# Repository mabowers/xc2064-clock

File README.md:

# xc2064-clock
Desk clock based on the Xilinx XC2064 FPGA

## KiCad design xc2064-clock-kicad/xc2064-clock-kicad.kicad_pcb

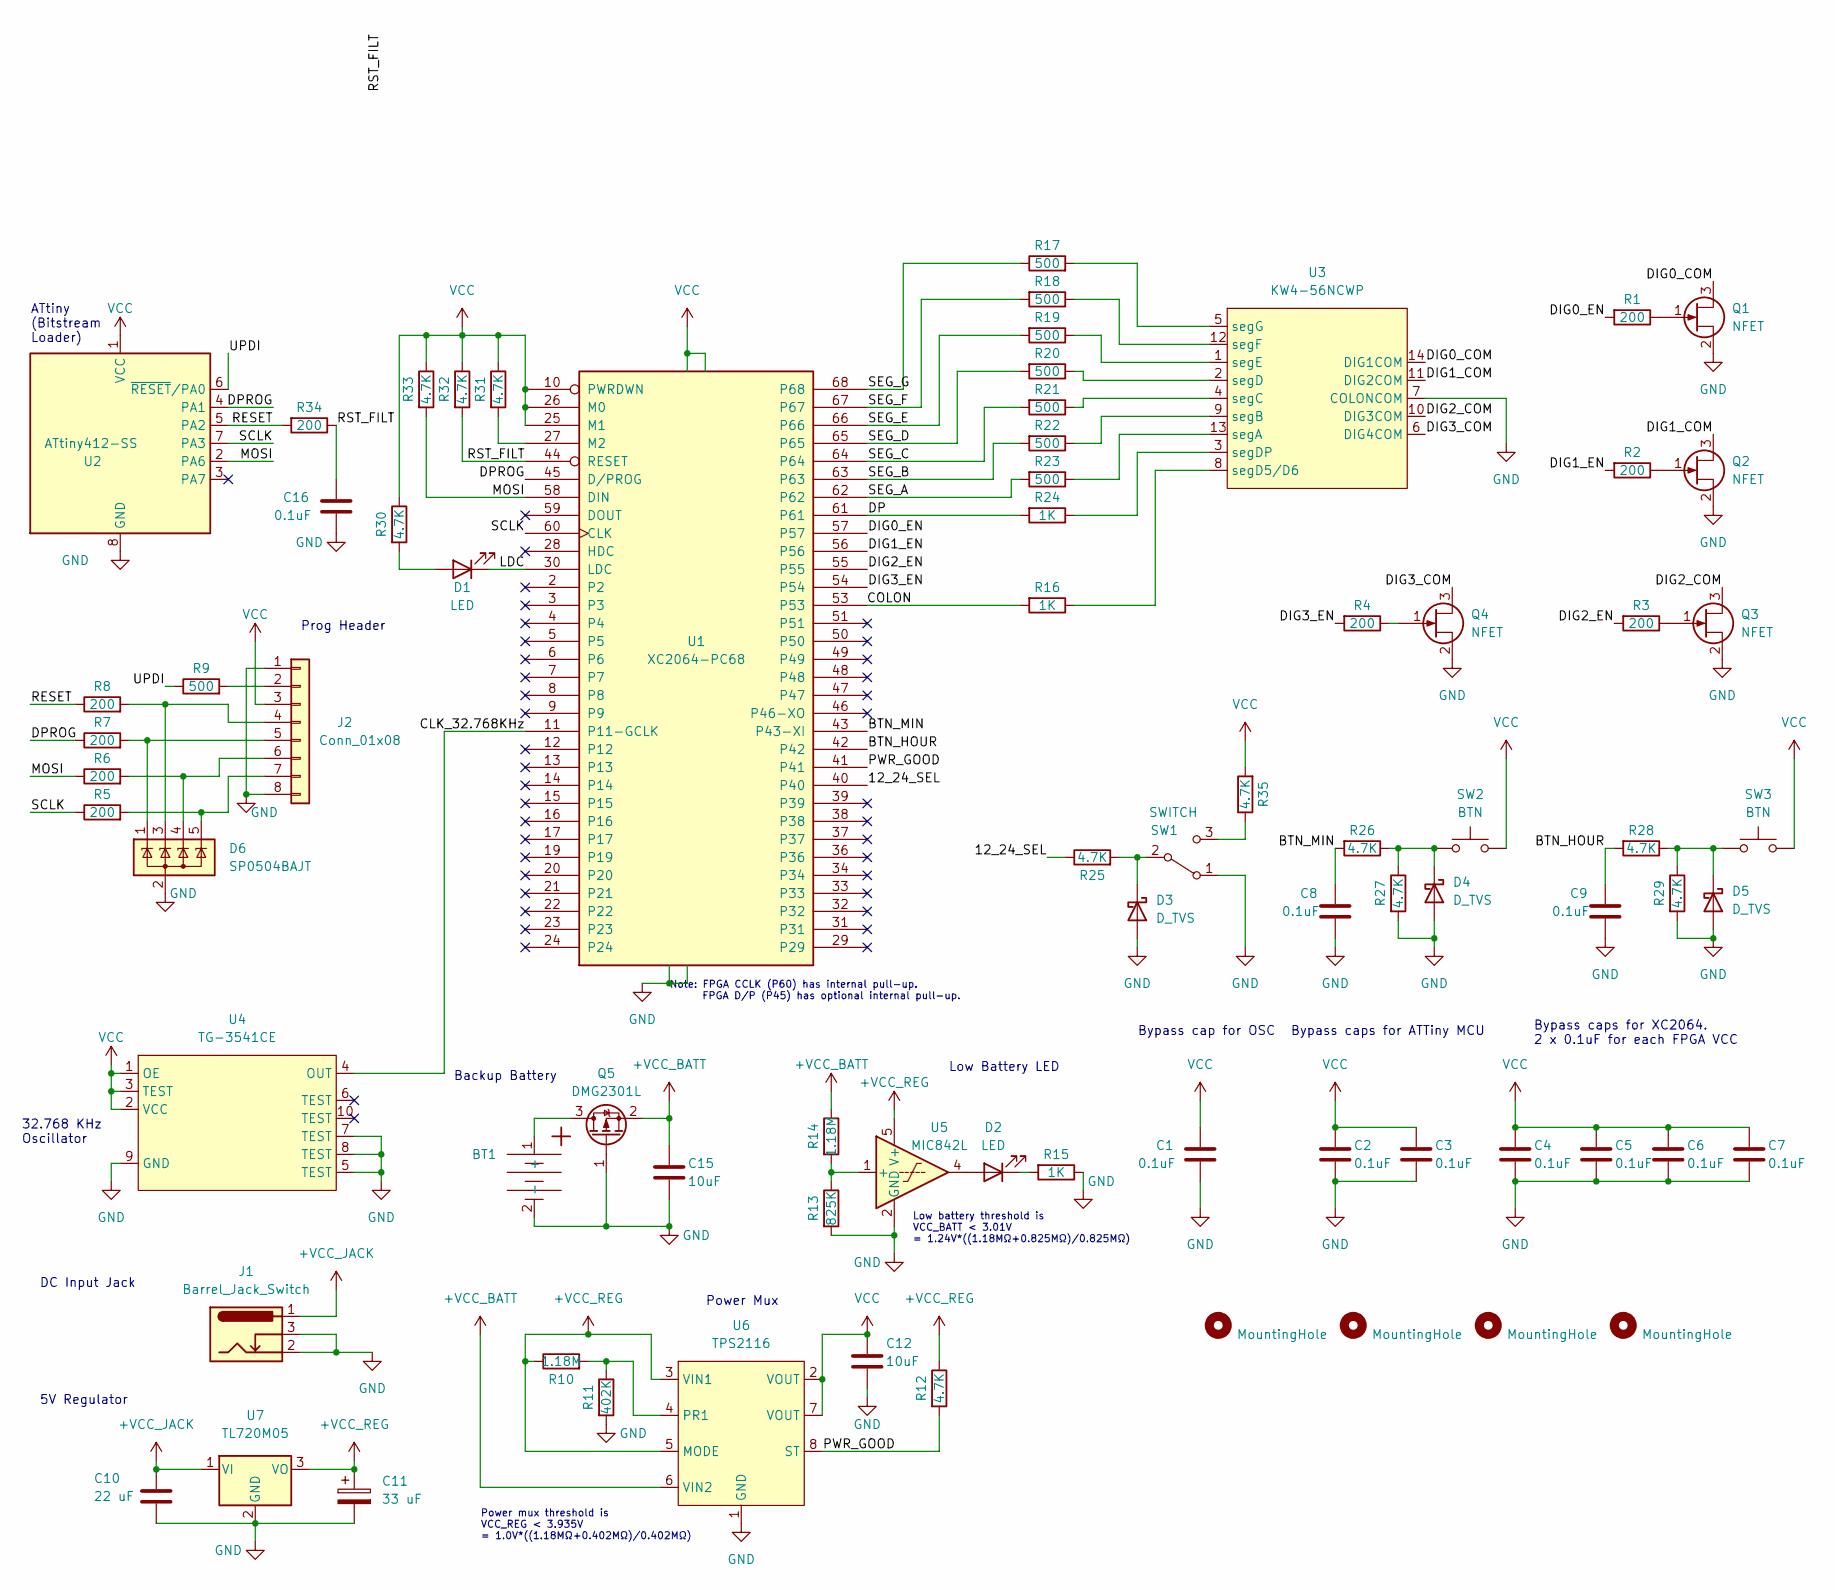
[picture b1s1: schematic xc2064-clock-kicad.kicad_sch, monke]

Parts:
BT1: 3PACK_AAA; BatteryHolder_3AAA
C1, C2, C3, C4, C5, C6, C7, C8, C9, C16: 0.1uF; C_0603_1608Metric_Pad1.08x0.95mm_HandSolder
C10: 22 uF; C_1206_3216Metric_Pad1.33x1.80mm_HandSolder
C11: 33 uF; CP_EIA-3528-21_Kemet-B_Pad1.50x2.35mm_HandSolder
C12, C15: 10uF; C_0805_2012Metric_Pad1.18x1.45mm_HandSolder
D1, D2: LED; R_0603_1608Metric_Pad0.98x0.95mm_HandSolder
D3, D4, D5: D_TVS; D_SOD-523
D6: SP0504BAJT; SOT-353_SC-70-5
H1, H2, H3, H4: MountingHole; MountingHole_3mm_Pad
J1: Barrel_Jack_Switch; SMTBarrelJack
J2: Conn_01x08; PinHeader_1x08_P2.54mm_Vertical
Q1, Q2, Q3, Q4: NFET; SOT-23
Q5: DMG2301L; SOT-23
R1, R2, R3, R4, R5, R6, R7, R8, R34: 200; R_0603_1608Metric_Pad0.98x0.95mm_HandSolder
R9, R17, R18, R19, R20, R21, R22, R23: 500; R_0603_1608Metric_Pad0.98x0.95mm_HandSolder
R10, R14: 1.18M; R_0603_1608Metric_Pad0.98x0.95mm_HandSolder
R11: 402K; R_0603_1608Metric_Pad0.98x0.95mm_HandSolder
R12, R25, R26, R27, R28, R29, R30, R31, R32, R33, R35: 4.7K; R_0603_1608Metric_Pad0.98x0.95mm_HandSolder
R13: 825K; R_0603_1608Metric_Pad0.98x0.95mm_HandSolder
R15, R16, R24: 1K; R_0603_1608Metric_Pad0.98x0.95mm_HandSolder
SW1: SWITCH; SW_CuK_OS102011MA1QN1_SPDT_Angled
SW2, SW3: BTN; SW_Tactile_SPST_Angled_PTS645Vx58-2LFS
U1: XC2064-PC68; PLCC-68_SMD-Socket_excelsior
U2: ATtiny412-SS; SOIC-8_3.9x4.9mm_P1.27mm
U3: KW4-56NCWP; KW4-56NXWB-P-Y
U4: TG-3541CE
U5: MIC842L; SOT-353_SC-70-5
U6: TPS2116; SOT5x3
U7: TL720M05; TO-252-2

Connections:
+VCC_BATT: C15.1, Q5.2 (S), R14.1, U6.6 (VIN2)
+VCC_JACK: C10.1, J1.1, U7.1 (VI)
+VCC_REG: C11.1, R10.1, R12.1, U5.5 (V+), U6.3 (VIN1), U6.5 (MODE), U7.3 (VO)
/12_24_SEL: R25.1, U1.40
/BTN_HOUR: C9.1, R28.2, U1.42
/BTN_MIN: C8.1, R26.2, U1.43 (P43-XI)
/CLK_32.768KHz: U1.11 (P11-GCLK), U4.4 (OUT)
/COLON: R16.2, U1.53
/DIG0_COM: Q1.3 (D), U3.14 (DIG1COM)
/DIG0_EN: R1.2, U1.57
/DIG1_COM: Q2.3 (D), U3.11 (DIG2COM)
/DIG1_EN: R2.2, U1.56
/DIG2_COM: Q3.3 (D), U3.10 (DIG3COM)
/DIG2_EN: R3.2, U1.55
/DIG3_COM: Q4.3 (D), U3.6 (DIG4COM)
/DIG3_EN: R4.2, U1.54
/DP: R24.2, U1.61
/DPROG: R7.1, U1.45 (D/PROG), U2.4 (PA1)
/LDC: D1.1 (K), U1.30 (LDC)
/MOSI: R6.1, R33.2, U1.58 (DIN), U2.2 (PA6)
/PWR_GOOD: R12.2, U1.41, U6.8 (ST)
/RESET: R8.1, R34.2, U2.5 (PA2)
/RST_FILT: C16.1, R32.2, R34.1, U1.44 (RESET)
/SCLK: R5.1, U1.60 (CLK), U2.7 (PA3)
/SEG_A: R23.2, U1.62
/SEG_B: R22.2, U1.63
/SEG_C: R21.2, U1.64
/SEG_D: R20.2, U1.65
/SEG_E: R19.2, U1.66
/SEG_F: R18.2, U1.67
/SEG_G: R17.1, U1.68
/UPDI: R9.1, U2.6 (~RESET/PA0)
GND: BT1.2 (-), C1.2, C2.2, C3.2, C4.2, C5.2, C6.2, C7.2, C8.2, C9.2, C10.2, C11.2, C12.2, C15.2, C16.2, D3.2 (A), D4.2 (A), D5.2 (A), D6.2 (A), J1.2, J1.3, J2.1, J2.8, Q1.2 (S), Q2.2 (S), Q3.2 (S), Q4.2 (S), Q5.1 (G), R11.2, R13.2, R15.1, R27.2, R29.2, SW1.1 (A), U1.1 (GND), U1.35 (GND), U2.8 (GND), U3.7 (COLONCOM), U4.5 (TEST), U4.7 (TEST), U4.8 (TEST), U4.9 (GND), U5.2 (GND), U6.1 (GND), U7.2 (GND)
unnamed: BT1.1 (+), Q5.3 (D)
unnamed: D1.2 (A), R30.2
unnamed: D2.1 (K), R15.2
unnamed: D2.2 (A), U5.4
unnamed: D3.1 (K), R25.2, SW1.2 (B)
unnamed: D4.1 (K), R26.1, R27.1, SW2.1
unnamed: D5.1 (K), R28.1, R29.1, SW3.1
unnamed: D6.1 (K), J2.5, R7.2
unnamed: D6.3 (K), J2.4, R8.2
unnamed: D6.4 (K), J2.6, R6.2
unnamed: D6.5 (K), J2.7, R5.2
unnamed: J2.2, R9.2
unnamed: Q1.1 (G), R1.1
unnamed: Q2.1 (G), R2.1
unnamed: Q3.1 (G), R3.1
unnamed: Q4.1 (G), R4.1
unnamed: R10.2, R11.1, U6.4 (PR1)
unnamed: R13.1, R14.2, U5.1 (+)
unnamed: R16.1, U3.8 (segD5/D6)
unnamed: R17.2, U3.5 (segG)
unnamed: R18.1, U3.12 (segF)
unnamed: R19.1, U3.1 (segE)
unnamed: R20.1, U3.2 (segD)
unnamed: R21.1, U3.4 (segC)
unnamed: R22.1, U3.9 (segB)
unnamed: R23.1, U3.13 (segA)
unnamed: R24.1, U3.3 (segDP)
unnamed: R31.2, U1.27 (M2)
unnamed: R35.1, SW1.3 (C)
VCC: C1.1, C2.1, C3.1, C4.1, C5.1, C6.1, C7.1, C12.1, J2.3, R30.1, R31.1, R32.1, R33.1, R35.2, SW2.2, SW3.2, U1.10 (PWRDWN), U1.18 (VCC), U1.25 (M1), U1.26 (M0), U1.52 (VCC), U2.1 (VCC), U4.1 (OE), U4.2 (VCC), U4.3 (TEST), U6.2 (VOUT), U6.7 (VOUT)

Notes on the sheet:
Bypass caps for XC2064. 2 x 0.1uF for each FPGA VCC
DC Input Jack
Power Mux
Note: FPGA CCLK (P60) has internal pull-up. FPGA D/P (P45) has optional internal pull-up.
Bypass caps for ATTiny MCU
Power mux threshold is VCC_REG < 3.935V = 1.0V*((1.18MΩ+0.402MΩ)/0.402MΩ)
ATtiny (Bitstream Loader)
Backup Battery
5V Regulator
Low Battery LED
Prog Header
Low battery threshold is VCC_BATT < 3.01V = 1.24V*((1.18MΩ+0.825MΩ)/0.825MΩ)
Bypass cap for OSC
32.768 KHz Oscillator

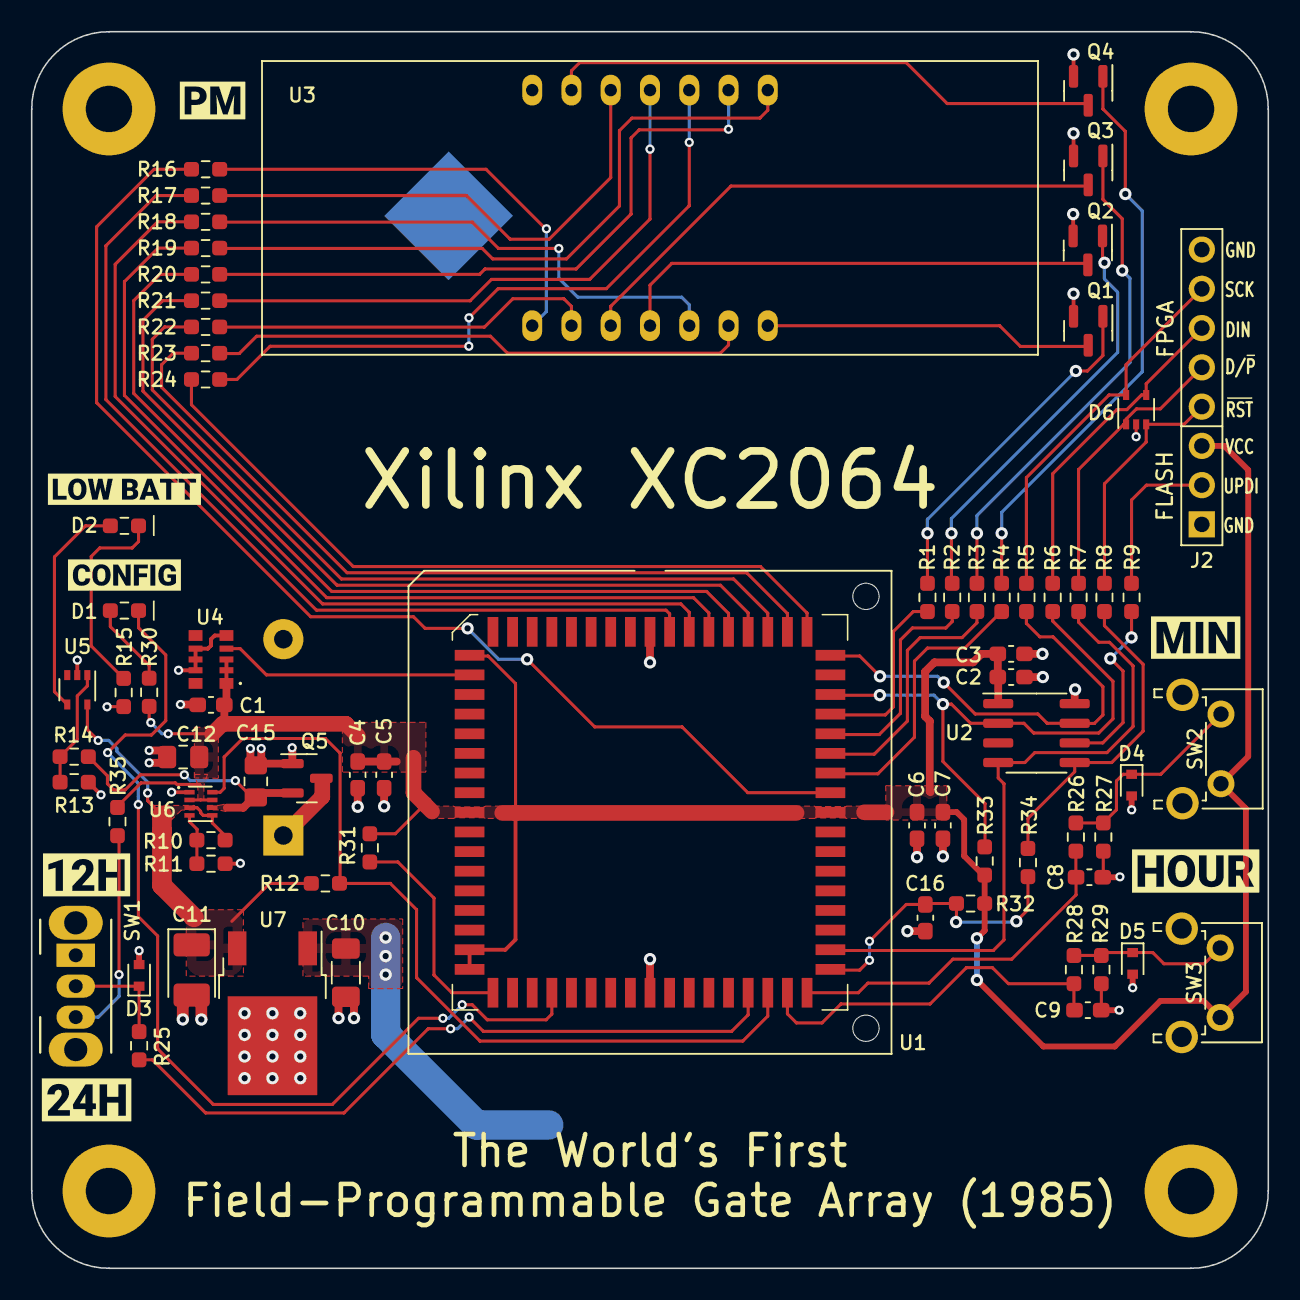
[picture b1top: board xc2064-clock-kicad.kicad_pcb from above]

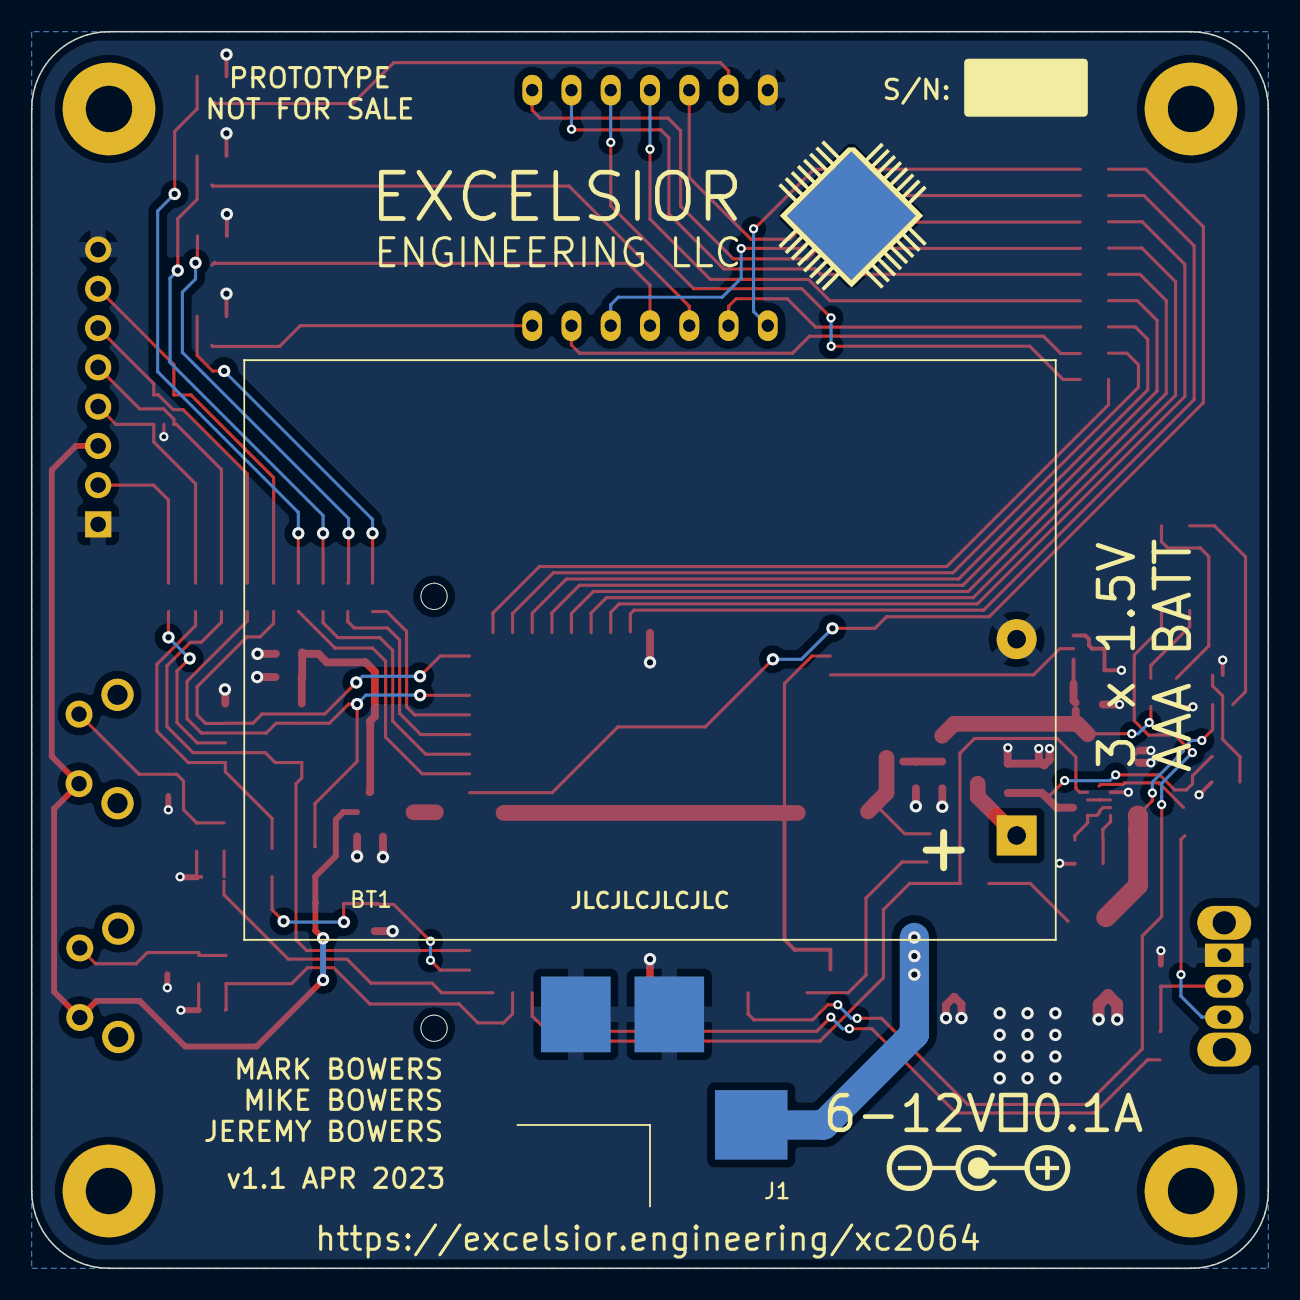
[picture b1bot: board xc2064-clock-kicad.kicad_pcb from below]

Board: 2 copper layers, 80.0 x 80.0 mm, 84 parts (2 on the bottom side), 63 nets.

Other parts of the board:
kibuzzard-63BF0C9B: G***; kibuzzard-63BF0C9B
kibuzzard-63BF0CA3: G***; kibuzzard-63BF0CA3
kibuzzard-63BF0CBF: G***; kibuzzard-63BF0CBF
kibuzzard-63BF0CD2: G***; kibuzzard-63BF0CD2
kibuzzard-63BF0CDA: G***; kibuzzard-63BF0CDA
kibuzzard-63BF0CE3: G***; kibuzzard-63BF0CE3
kibuzzard-63BF11B2: G***; kibuzzard-63BF11B2

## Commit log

2023-04-23 Add DOSBox C drive with Xilinx XACT 5 and OrCAD 4.4 pre-installed
2023-04-26 added kicad project
2023-04-26 updated gitignore for kicad proj
2023-04-26 rm tmp file
2023-04-26 Add missing C:/ORCAD/TEMPLATE/ files. Update install steps and .gitignore.
2023-04-26 Add Docker image for XC2064 development
2023-04-27 add custom part libraries (.pretty Footprints and kicad_sym Symbols)
2023-04-27 Add ATtiny412 compiler to Docker
2023-04-27 Initial commit of ATtiny412 bitstream loader
2023-04-27 Add makefile and ELF for Atmel XC2064 loader
